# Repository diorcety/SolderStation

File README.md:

# SolderStation
See the project description on the Electrolab wiki: wiki.electrolab.fr/Projets:SolderStationWEnglish

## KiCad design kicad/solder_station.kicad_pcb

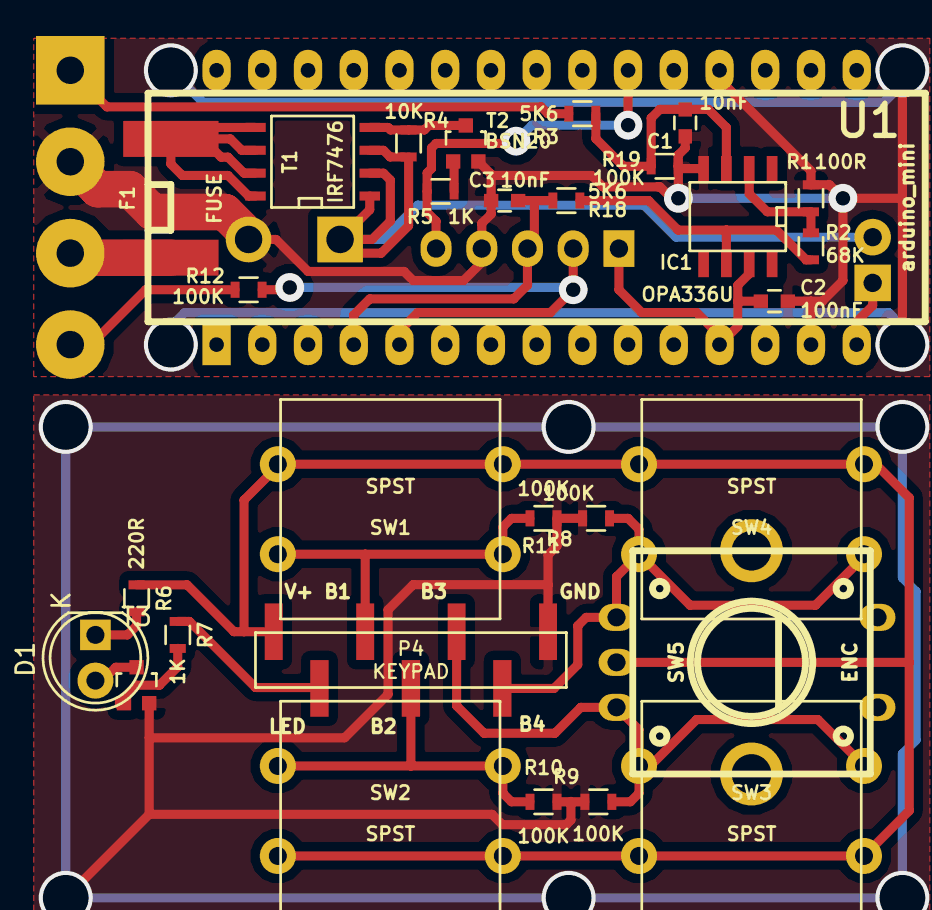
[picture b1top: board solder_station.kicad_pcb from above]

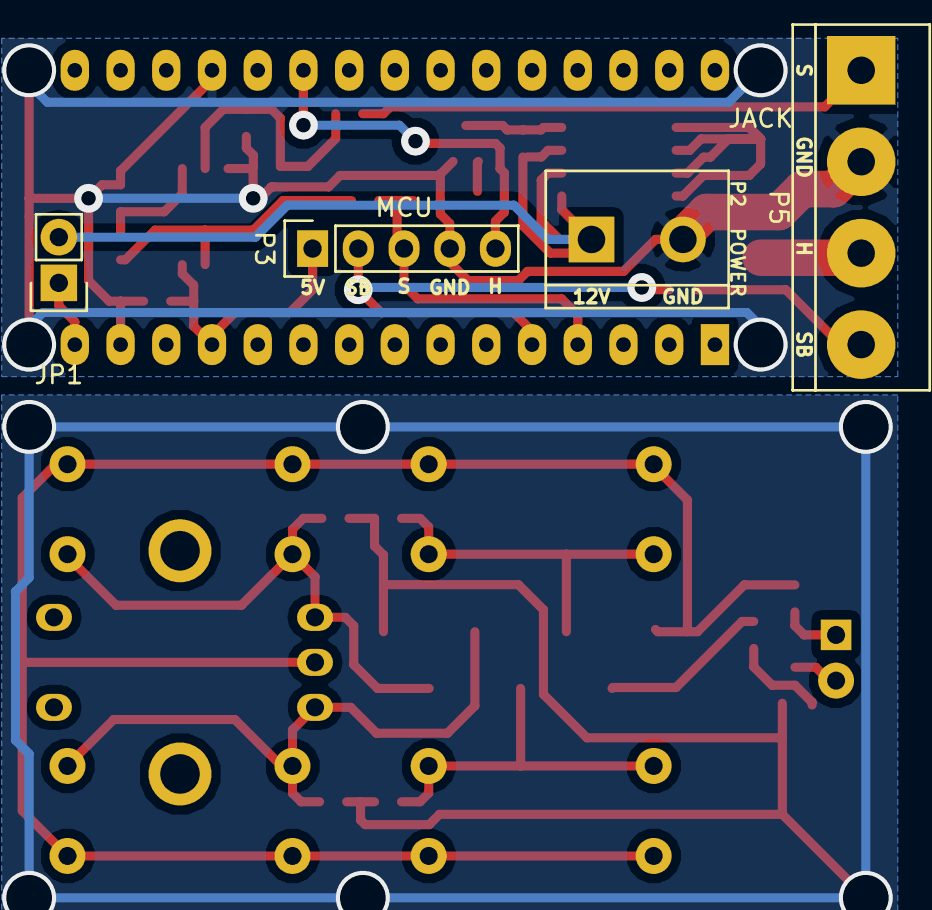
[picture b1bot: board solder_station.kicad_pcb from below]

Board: 2 copper layers, 34 parts (4 on the bottom side), 26 nets.

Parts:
C1, C3: 10nF; C_0603
C2: 100nF; C_0603
D1: LED; LED-5MM
F1: FUSE; SMD-3121
IC1: OPA336U; SOIC-8-W
JP1: JUMPER; Pin_Header_Straight_1x02
P2: POWER; bornier2
P3: MCU; Pin_Header_Straight_1x05
P4: KEYPAD; SMT1x7
P5: JACK; bornier4
R1: 100R; R_0603
R2: 68K; R_0603
R3, R18: 5K6; R_0603
R4: 10K; R_0603
R5, R7: 1K; R_0603
R6: 220R; R_0603
R8, R9, R10, R11, R12, R19: 100K; R_0603
SW1, SW2, SW3, SW4: SPST; SW_125_50
SW5: ENC; encoder_alps-ec12d
T1: IRF7476; SOIC-8-N
T2, T3: BSN20; Diode_SOT23
U1: arduino_mini

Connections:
+5V: C2.1, IC1.7, P3.1, U1.12
+12V: JP1.2, P2.1, R4.2, T1.1, T1.2, T1.3
GND: C1.2, C2.2, C3.2, IC1.4, P2.2, P3.4, P5.2, R1.2, R19.2, T2.2, U1.14, U1.19
HEATER: F1.2, P5.3
MCU_HEATER: P3.5, R5.1, U1.21
MCU_SENSOR: C3.1, P3.3, R18.1, U1.4
MCU_STANDBY: P3.2, R12.2, U1.5
unnamed: C1.1, IC1.3, R3.1, R19.1
unnamed: D1.1, R6.1
unnamed: D1.2, T3.3
unnamed: F1.1, T1.5, T1.6, T1.7, T1.8
unnamed: IC1.2, R1.1, R2.2
unnamed: IC1.6, R2.1, R18.2
unnamed: JP1.1, U1.15
unnamed: R4.1, T1.4, T2.3
unnamed: R5.2, T2.1
unnamed: R7.1, T3.1
PIN_B1: P4.3, R11.1, SW1.2
PIN_B2: P4.4, R10.1, SW2.2
PIN_B3: P4.5, R9.1, SW3.2, SW5.3
PIN_B4: P4.6, R8.1, SW4.2, SW5.1
PIN_GND: P4.7, R8.2, R9.2, R10.2, R11.2, T3.2
PIN_LED: P4.2, R7.2
PIN_V+: P4.1, R6.2, SW1.1, SW2.1, SW3.1, SW4.1, SW5.2
SENSOR: P5.1, R3.2
STANDBY: P5.4, R12.1

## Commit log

2015-01-14 Add kicad project
2015-01-18 Add arduino nano shield footprint
2015-02-09 Improve arduino code
2015-02-09 Add Alimentation and connector parts
2015-02-12 Improve arduino code (menu)
2015-03-04 Improve power switch
2015-03-04 Add Preprocessor configurations
2015-03-05 Add original behaviour & configuration
2015-03-05 Reduce RAM usage
2015-03-05 Avoid new allocation using new placement
2015-03-13 Configurable step
2015-04-01 Add Rotary encode for Marc version
2015-04-22 Update kicad project
2015-04-28 Improve LCD display
2015-04-30 Improve display of LCD
2015-05-03 Fix compilation without LCD
2015-05-03 Seg7: Dot pwm indication
2015-05-05 Add Overheat protection
2015-05-06 Use Analogique notations instead of digital ones
2015-05-06 Fix MO prototype pinout
2015-05-06 Remove Draw debug logging
2015-05-06 Update Arduino-Makefile
2015-05-06 Improve configuration switch
2015-05-06 Remove useless logs
2015-05-07 Invert digit weight for MO config
2015-05-07 Change error message for seg7
2015-05-07 No default configuration
2015-05-19 Add memory settings preprocessor switch
2015-05-21 Update kicad pcb
2015-05-21 Add missing settings logging
2015-05-21 Improve logging and heat protection
2015-05-21 Ignore completly settingsTimer
2015-05-22 Update circuit
2015-05-23 Add rotative encoder
2015-05-23 Use 12x12 mm button
2015-05-26 Fix rasnet size
2015-05-27 Add missing track
2015-06-03 Rework pcb for iron toner transfer
2015-06-03 Fix memory issue and add divider for rotary button
2015-06-04 Add LCD ST7735 module
2015-06-04 Fix language issue
2015-06-04 Fix translation for small screen
2015-06-04 LCD optimizations
2015-06-09 Rename MO config to ELECTROLAB config
2015-06-10 Add via instead of go under resistors
2015-06-11 Fix electrolab config
2015-06-16 Add iron temperature meaning
2015-06-16 Add switch for temperature average feature
2015-06-16 Add preprocessor check on TEMP_MEAN value
2015-06-16 Fix mean count computation and comment
2015-06-16 Add iron temperature refresh time (avoid artifact on display)
2015-07-10 Add VIN jumper
2015-07-15 Add standby display for seg7 module
2015-07-15 Adjust standby temperature
2015-07-26 Fix buttons configuration in xxx profile
2015-07-26 Feedback improvement of PCB
2015-07-30 Fix some configuration settings
2015-07-30 Set electrolab standby temperature to 20
2015-08-13 Use serial baud from configuration file
2015-10-03 Add a watchdog in order to prevent overheat if the arduino hangs
2015-11-15 Change electrolab direction of rotation
2015-11-17 Add edit behaviours
2015-11-17 Update display according to the new behaviours
2015-11-19 Fix previous commit preprocessor
2015-11-19 Force at start to not heat the iron
2015-12-17 Fix some warnings
2015-12-17 Only write to the eeprom if there is an update
2015-12-17 Add makefile warning errors Add eeprom offset in order to avoid known 0 eeprom address corruption (not sure) Enforce check on eeprom values
2016-03-18 Fix LCD display of the temperatures
2016-04-05 Update Adafruit libraries
2016-04-05 Create README.md
    From the electrolab wiki
2016-04-05 Add drop protection
2016-04-06 Remove kicad directory
2019-06-06 Add modifiable iron gain
